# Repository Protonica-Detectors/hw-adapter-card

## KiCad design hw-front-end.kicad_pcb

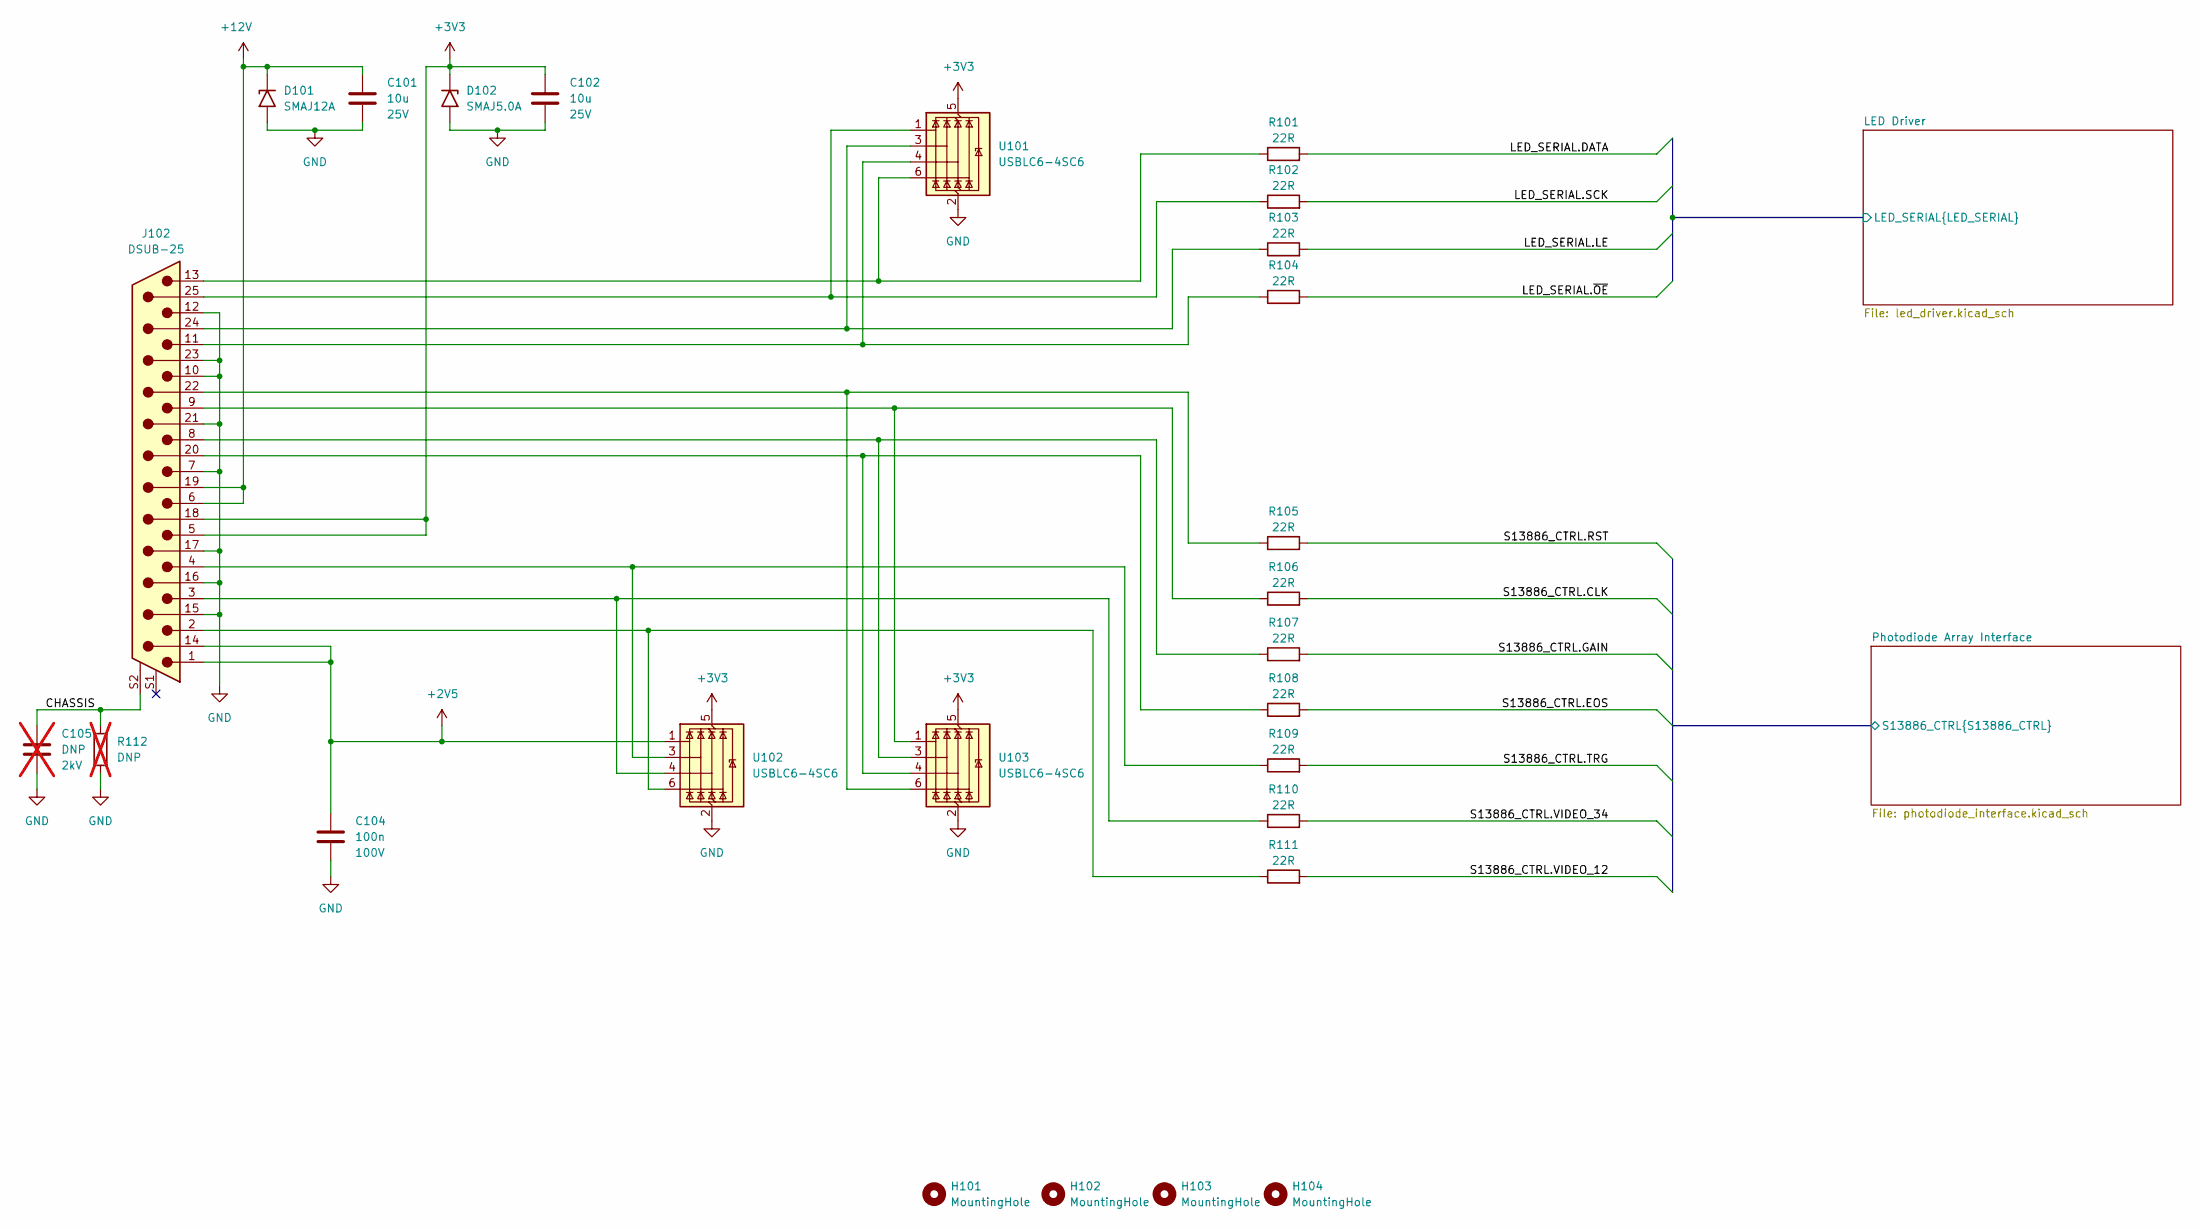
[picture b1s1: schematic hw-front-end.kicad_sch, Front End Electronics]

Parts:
C101, C102: 10u; C_1206_3216Metric_Pad1.33x1.80mm_HandSolder; Voltage 25V; MPN GRM31CR71E106KA12L
C104: 100n; C_0805_2012Metric_Pad1.18x1.45mm_HandSolder; Voltage 100V; MPN GCM21BR72A104KA37L
C105: DNP; C_1206_3216Metric_Pad1.33x1.80mm_HandSolder; Voltage 2kV; not fitted
D101: SMAJ12A; D_SMA; MPN SMAJ12A
D102: SMAJ5.0A; D_SMA; MPN SMAJ5.0A
H101, H102, H103, H104: MountingHole; MountingHole_3.2mm_M3_DIN965
J102: DSUB-25; J_Wurth_WR-DSUB_618025231221; MPN 618025231221
R101, R102, R103, R104, R105, R106, R107, R108, R109, R110, R111: 22R; R_0805_2012Metric_Pad1.20x1.40mm_HandSolder; MPN CRCW080522R0FKEA
R112: DNP; R_1206_3216Metric_Pad1.30x1.75mm_HandSolder; not fitted
U101, U102, U103: USBLC6-4SC6; SOT-23-6; MPN USBLC6-4SC6

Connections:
+2V5: C104.1, J102.1, J102.14, U102.1 (I/O1); also elsewhere on the board
+3V3: C102.1, D102.1 (A1), J102.5, J102.18, U101.5 (VBUS), U102.5 (VBUS), U103.5 (VBUS); also elsewhere on the board
+12V: C101.1, D101.1 (A1), J102.6, J102.19; also elsewhere on the board
/CHASSIS: C105.1, J102.S2 (SHIELD), R112.1
/LED Driver/LED_SERIAL.DATA: R101.2; also elsewhere on the board
/LED Driver/LED_SERIAL.LE: R103.2; also elsewhere on the board
/LED Driver/LED_SERIAL.SCK: R102.2; also elsewhere on the board
/LED Driver/LED_SERIAL.~OE: R104.2; also elsewhere on the board
/Photodiode Array Interface/S13886_CTRL.CLK: R106.2; also elsewhere on the board
/Photodiode Array Interface/S13886_CTRL.EOS: R108.2; also elsewhere on the board
/Photodiode Array Interface/S13886_CTRL.GAIN: R107.2; also elsewhere on the board
/Photodiode Array Interface/S13886_CTRL.RST: R105.2; also elsewhere on the board
/Photodiode Array Interface/S13886_CTRL.TRG: R109.2; also elsewhere on the board
/Photodiode Array Interface/S13886_CTRL.VIDEO_12: R111.2; also elsewhere on the board
/Photodiode Array Interface/S13886_CTRL.VIDEO_34: R110.2; also elsewhere on the board
GND: C101.2, C102.2, C104.2, C105.2, D101.2 (A2), D102.2 (A2), J102.7, J102.10, J102.12, J102.15, J102.16, J102.17, J102.21, J102.23, R112.2, U101.2 (GND), U102.2 (GND), U103.2 (GND); also elsewhere on the board
unnamed: J102.20, R108.1, U103.4 (I/O3)
unnamed: J102.22, R105.1, U103.6 (I/O4)
unnamed: J102.24, R103.1, U101.3 (I/O2)
unnamed: J102.25, R102.1, U101.1 (I/O1)
unnamed: J102.11, R104.1, U101.4 (I/O3)
unnamed: J102.13, R101.1, U101.6 (I/O4)
unnamed: J102.4, R109.1, U102.3 (I/O2)
unnamed: J102.3, R110.1, U102.4 (I/O3)
unnamed: J102.2, R111.1, U102.6 (I/O4)
unnamed: J102.9, R106.1, U103.1 (I/O1)
unnamed: J102.8, R107.1, U103.3 (I/O2)

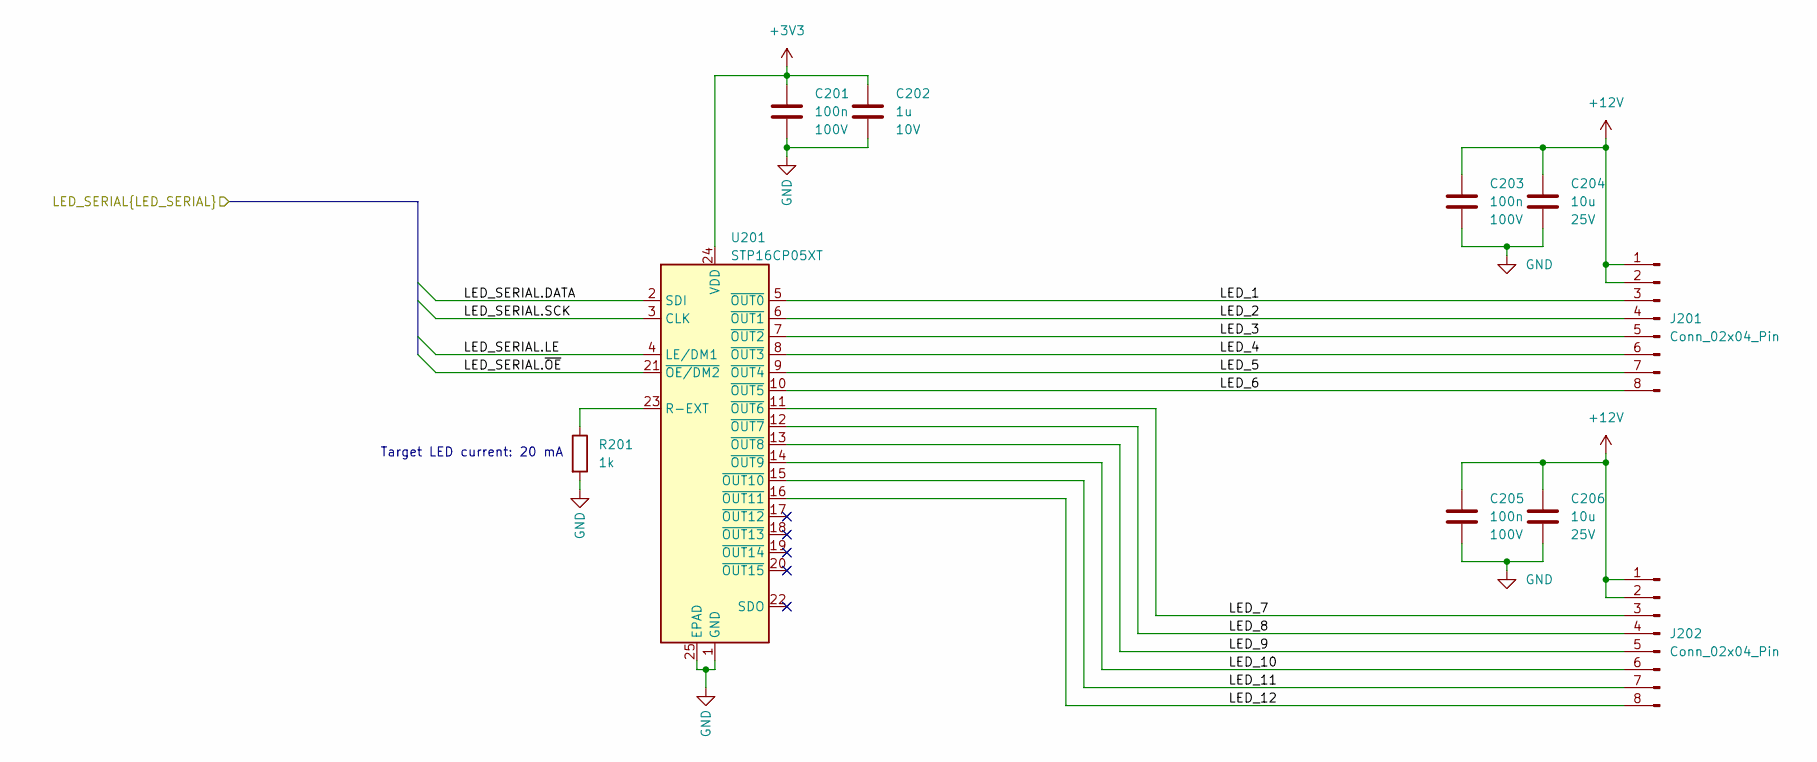
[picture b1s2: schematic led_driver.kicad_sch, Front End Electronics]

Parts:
C201, C203, C205: 100n; C_0805_2012Metric_Pad1.18x1.45mm_HandSolder; Voltage 100V; MPN GCM21BR72A104KA37L
C202: 1u; C_0805_2012Metric_Pad1.18x1.45mm_HandSolder; Voltage 10V; MPN GRM21BR71A105KA01L
C204, C206: 10u; C_1206_3216Metric_Pad1.33x1.80mm_HandSolder; Voltage 25V; MPN GRM31CR71E106KA12L
J201, J202: Conn_02x04_Pin; PinHeader_2x04_P2.54mm_Vertical; MPN M20-9760442
R201: 1k; R_0805_2012Metric_Pad1.20x1.40mm_HandSolder; MPN CRCW08051K00FKEA
U201: STP16CP05XT; HTSSOP-24-1EP_4.4x7.8mm_P0.65mm_EP3.2x5mm; MPN STP16CP05XTTR

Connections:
+3V3: C201.1, C202.1, U201.24 (VDD); also elsewhere on the board
+12V: C203.1, C204.1, C205.1, C206.1, J201.1, J201.2, J202.1, J202.2; also elsewhere on the board
/LED Driver/LED_1: J201.3, U201.5 (~OUT0)
/LED Driver/LED_2: J201.4, U201.6 (~OUT1)
/LED Driver/LED_3: J201.5, U201.7 (~OUT2)
/LED Driver/LED_4: J201.6, U201.8 (~OUT3)
/LED Driver/LED_5: J201.7, U201.9 (~OUT4)
/LED Driver/LED_6: J201.8, U201.10 (~OUT5)
/LED Driver/LED_7: J202.3, U201.11 (~OUT6)
/LED Driver/LED_8: J202.4, U201.12 (~OUT7)
/LED Driver/LED_9: J202.5, U201.13 (~OUT8)
/LED Driver/LED_10: J202.6, U201.14 (~OUT9)
/LED Driver/LED_11: J202.7, U201.15 (~OUT10)
/LED Driver/LED_12: J202.8, U201.16 (~OUT11)
/LED Driver/LED_SERIAL.DATA: U201.2 (SDI); also elsewhere on the board
/LED Driver/LED_SERIAL.LE: U201.4 (LE/DM1); also elsewhere on the board
/LED Driver/LED_SERIAL.SCK: U201.3 (CLK); also elsewhere on the board
/LED Driver/LED_SERIAL.~OE: U201.21 (~OE/DM2); also elsewhere on the board
GND: C201.2, C202.2, C203.2, C204.2, C205.2, C206.2, R201.2, U201.1 (GND), U201.25 (EPAD); also elsewhere on the board
unnamed: R201.1, U201.23 (R-EXT)

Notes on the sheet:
Target LED current: 20 mA

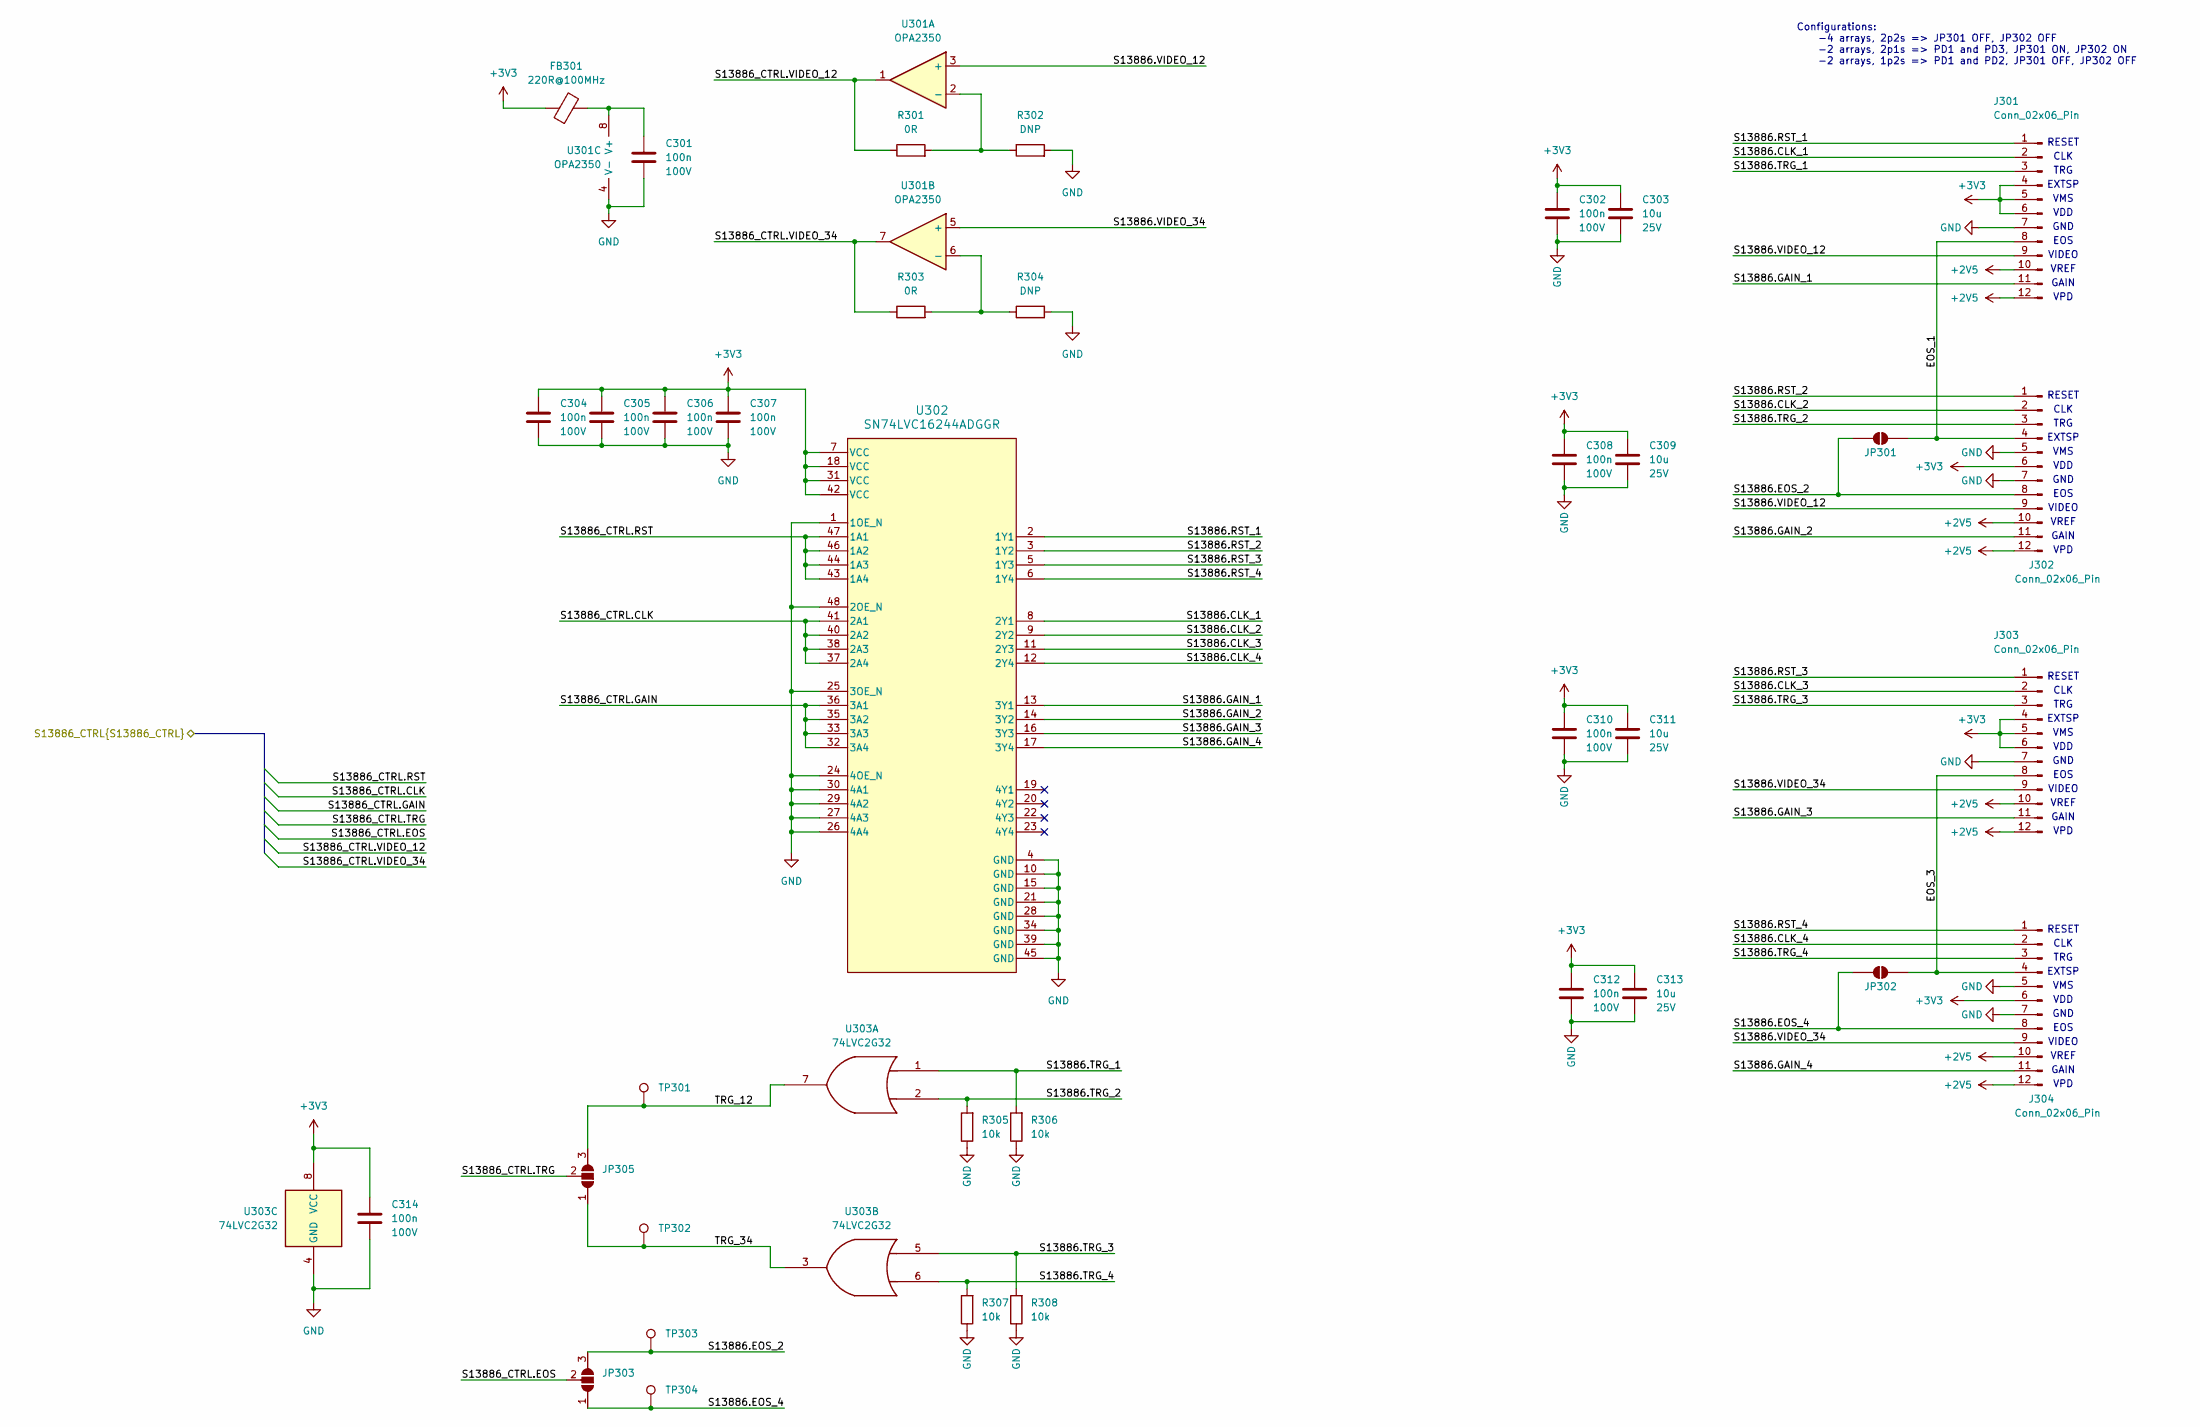
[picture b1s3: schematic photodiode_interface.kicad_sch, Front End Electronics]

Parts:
C301, C302, C304, C305, C306, C307, C308, C310, C312, C314: 100n; C_0805_2012Metric_Pad1.18x1.45mm_HandSolder; Voltage 100V; MPN GCM21BR72A104KA37L
C303, C309, C311, C313: 10u; C_1206_3216Metric_Pad1.33x1.80mm_HandSolder; Voltage 25V; MPN GRM31CR71E106KA12L
FB301: 220R@100MHz; L_0805_2012Metric_Pad1.05x1.20mm_HandSolder; MPN BLM21PG221SN1D
J301, J302, J303, J304: Conn_02x06_Pin; PinHeader_2x06_P2.54mm_Vertical; MPN M20-9760642
JP301, JP302: SolderJumper_2_Open; SolderJumper-2_P1.3mm_Open_Pad1.0x1.5mm
JP303, JP305: SolderJumper_3_Open; SolderJumper-3_P1.3mm_Open_Pad1.0x1.5mm
R301, R303: 0R; R_0805_2012Metric_Pad1.20x1.40mm_HandSolder; MPN CRCW08050000Z0EA
R302, R304: DNP; R_0805_2012Metric_Pad1.20x1.40mm_HandSolder
R305, R306, R307, R308: 10k; R_0805_2012Metric_Pad1.20x1.40mm_HandSolder; MPN CRCW080510K0FKEA
TP301, TP302, TP303, TP304: TestPoint; TestPoint_Keystone_5005-5009_Compact; MPN 5005
U301: OPA2350; SOIC-8_3.9x4.9mm_P1.27mm; MPN OPA2350UA/2K5
U302: SN74LVC16244ADGGR; TSSOP-48_6.1x12.5mm_P0.5mm; MPN SN74LVC16244ADGGR
U303: 74LVC2G32; VSSOP-8_3x3mm_P0.65mm; MPN SN74LVC2G32DCTR

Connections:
+2V5: J301.10, J301.12, J302.10, J302.12, J303.10, J303.12, J304.10, J304.12; also elsewhere on the board
+3V3: C302.1, C303.1, C304.1, C305.1, C306.1, C307.1, C308.1, C309.1, C310.1, C311.1, C312.1, C313.1, C314.1, FB301.1, J301.4, J301.5, J301.6, J302.6, J303.4, J303.5, J303.6, J304.6, U302.7 (VCC), U302.18 (VCC), U302.31 (VCC), U302.42 (VCC), U303.8 (VCC); also elsewhere on the board
/Photodiode Array Interface/EOS_1: J301.8, J302.4, JP301.1 (A)
/Photodiode Array Interface/EOS_3: J303.8, J304.4, JP302.1 (A)
/Photodiode Array Interface/S13886.CLK_1: J301.2, U302.8 (2Y1)
/Photodiode Array Interface/S13886.CLK_2: J302.2, U302.9 (2Y2)
/Photodiode Array Interface/S13886.CLK_3: J303.2, U302.11 (2Y3)
/Photodiode Array Interface/S13886.CLK_4: J304.2, U302.12 (2Y4)
/Photodiode Array Interface/S13886.EOS_2: J302.8, JP301.2 (B), JP303.3 (B), TP303.1 (1_1)
/Photodiode Array Interface/S13886.EOS_4: J304.8, JP302.2 (B), JP303.1 (A), TP304.1 (1_1)
/Photodiode Array Interface/S13886.GAIN_1: J301.11, U302.13 (3Y1)
/Photodiode Array Interface/S13886.GAIN_2: J302.11, U302.14 (3Y2)
/Photodiode Array Interface/S13886.GAIN_3: J303.11, U302.16 (3Y3)
/Photodiode Array Interface/S13886.GAIN_4: J304.11, U302.17 (3Y4)
/Photodiode Array Interface/S13886.RST_1: J301.1, U302.2 (1Y1)
/Photodiode Array Interface/S13886.RST_2: J302.1, U302.3 (1Y2)
/Photodiode Array Interface/S13886.RST_3: J303.1, U302.5 (1Y3)
/Photodiode Array Interface/S13886.RST_4: J304.1, U302.6 (1Y4)
/Photodiode Array Interface/S13886.TRG_1: J301.3, R306.2, U303.1
/Photodiode Array Interface/S13886.TRG_2: J302.3, R305.2, U303.2
/Photodiode Array Interface/S13886.TRG_3: J303.3, R308.2, U303.5
/Photodiode Array Interface/S13886.TRG_4: J304.3, R307.2, U303.6
/Photodiode Array Interface/S13886.VIDEO_12: J301.9, J302.9, U301.3 (+)
/Photodiode Array Interface/S13886.VIDEO_34: J303.9, J304.9, U301.5 (+)
/Photodiode Array Interface/S13886_CTRL.CLK: U302.37 (2A4), U302.38 (2A3), U302.40 (2A2), U302.41 (2A1); also elsewhere on the board
/Photodiode Array Interface/S13886_CTRL.EOS: JP303.2 (C); also elsewhere on the board
/Photodiode Array Interface/S13886_CTRL.GAIN: U302.32 (3A4), U302.33 (3A3), U302.35 (3A2), U302.36 (3A1); also elsewhere on the board
/Photodiode Array Interface/S13886_CTRL.RST: U302.43 (1A4), U302.44 (1A3), U302.46 (1A2), U302.47 (1A1); also elsewhere on the board
/Photodiode Array Interface/S13886_CTRL.TRG: JP305.2 (C); also elsewhere on the board
/Photodiode Array Interface/S13886_CTRL.VIDEO_12: R301.1, U301.1; also elsewhere on the board
/Photodiode Array Interface/S13886_CTRL.VIDEO_34: R303.1, U301.7; also elsewhere on the board
/Photodiode Array Interface/TRG_12: JP305.3 (B), TP301.1 (1_1), U303.7
/Photodiode Array Interface/TRG_34: JP305.1 (A), TP302.1 (1_1), U303.3
GND: C301.2, C302.2, C303.2, C304.2, C305.2, C306.2, C307.2, C308.2, C309.2, C310.2, C311.2, C312.2, C313.2, C314.2, J301.7, J302.5, J302.7, J303.7, J304.5, J304.7, R302.2, R304.2, R305.1, R306.1, R307.1, R308.1, U301.4 (V-), U302.1 (1OE_N), U302.4 (GND), U302.10 (GND), U302.15 (GND), U302.21 (GND), U302.24 (4OE_N), U302.25 (3OE_N), U302.26 (4A4), U302.27 (4A3), U302.28 (GND), U302.29 (4A2), U302.30 (4A1), U302.34 (GND), U302.39 (GND), U302.45 (GND), U302.48 (2OE_N), U303.4 (GND); also elsewhere on the board
unnamed: R301.2, R302.1, U301.2 (-)
unnamed: R303.2, R304.1, U301.6 (-)
unnamed: C301.1, FB301.2, U301.8 (V+)

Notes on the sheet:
EXTSP
Configurations: -4 arrays, 2p2s => JP301 OFF, JP302 OFF -2 arrays, 2p1s => PD1 and PD3, JP301 ON, JP302 ON -2 arrays, 1p2s => PD1 and PD2, JP301 OFF, JP302 OFF
GND
TRG
VPD
VDD
VIDEO
CLK
EOS
GAIN
RESET
VMS
VREF

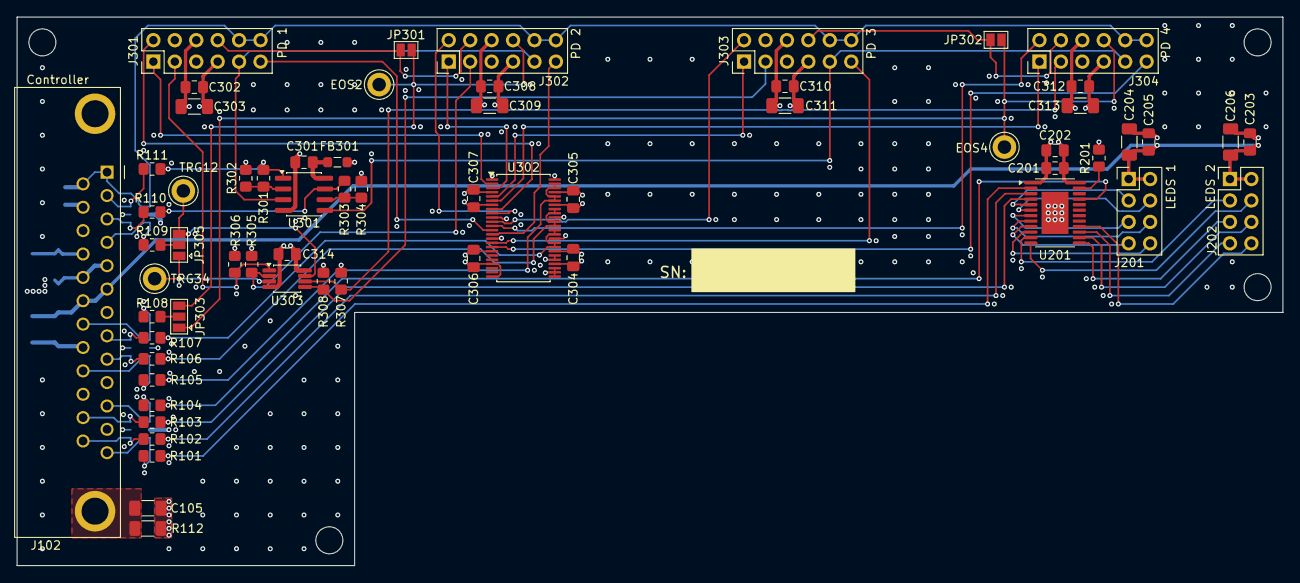
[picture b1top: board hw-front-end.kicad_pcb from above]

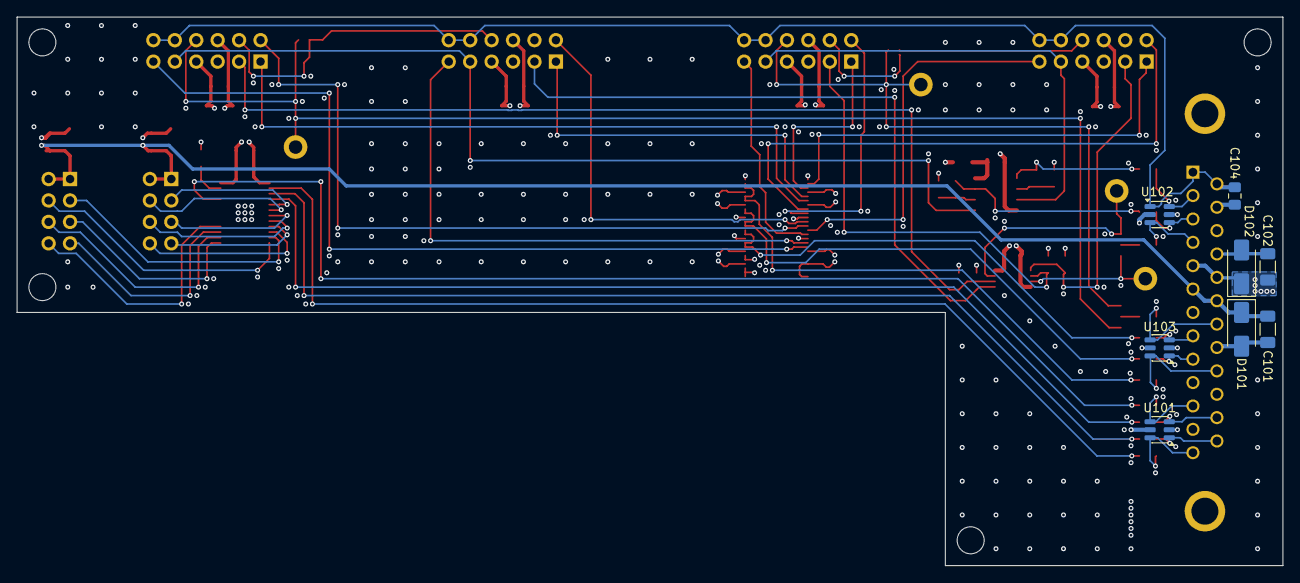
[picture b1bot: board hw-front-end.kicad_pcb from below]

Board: 6 copper layers, 150.0 x 65.0 mm, 74 parts (8 on the bottom side), 67 nets.

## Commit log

2026-04-23 schematic creation ongoing rev B.1
2026-04-29 erc clrean
2026-05-05 nodified according to review
2026-05-05 minor changes
2026-05-28 footprints associated to symbols
2026-06-10 Most tracks routed
2026-06-10 DRC clean
2026-06-11 added stitching vias and silkscreen
2026-06-15 updated bom, ready for ordering
